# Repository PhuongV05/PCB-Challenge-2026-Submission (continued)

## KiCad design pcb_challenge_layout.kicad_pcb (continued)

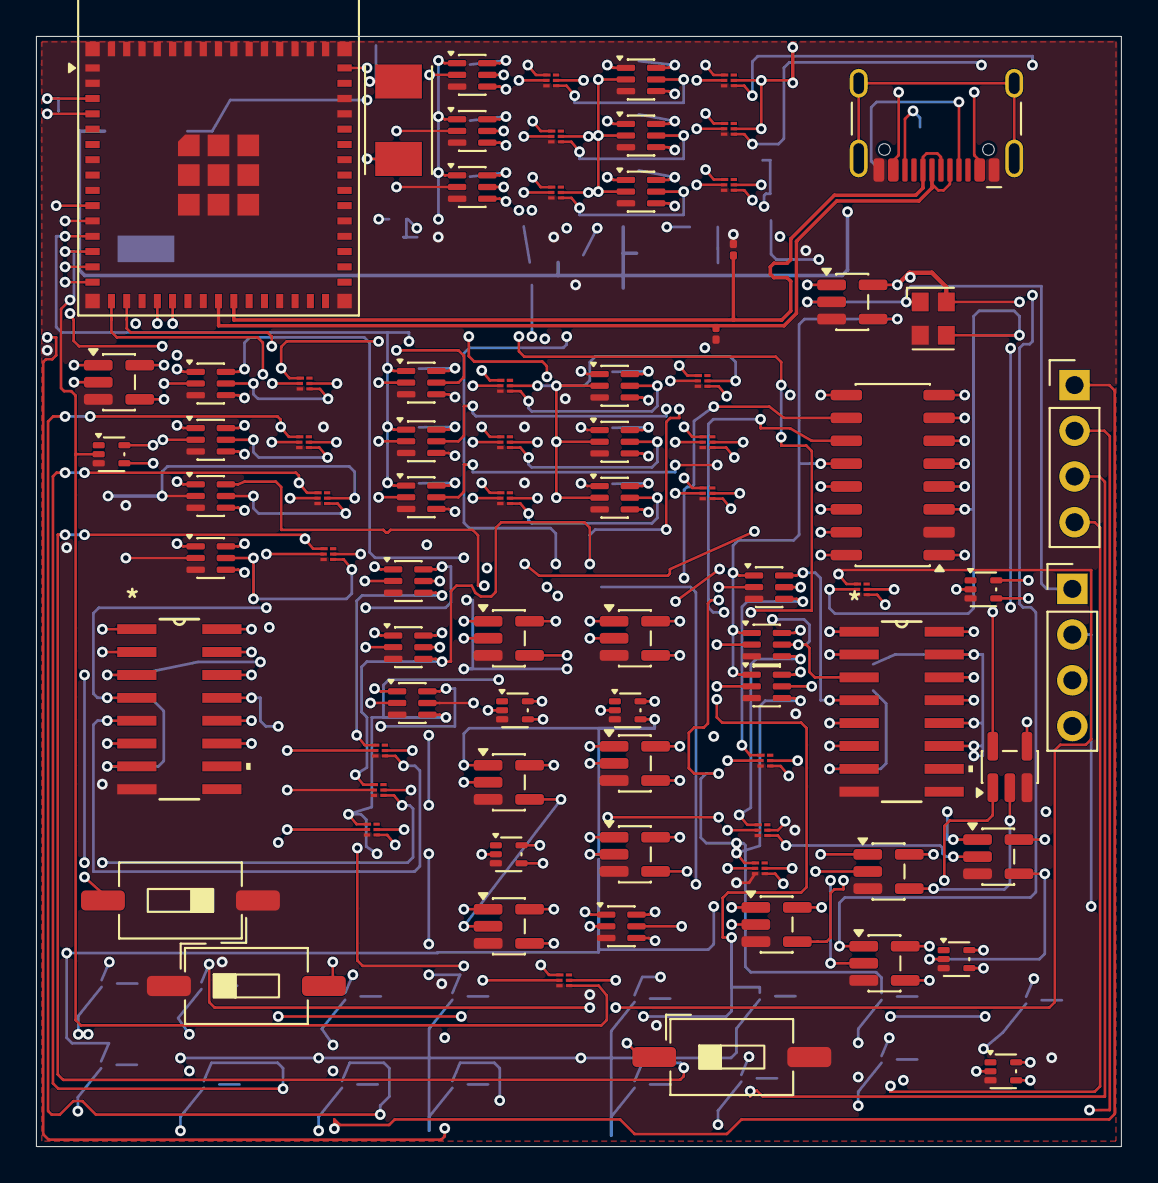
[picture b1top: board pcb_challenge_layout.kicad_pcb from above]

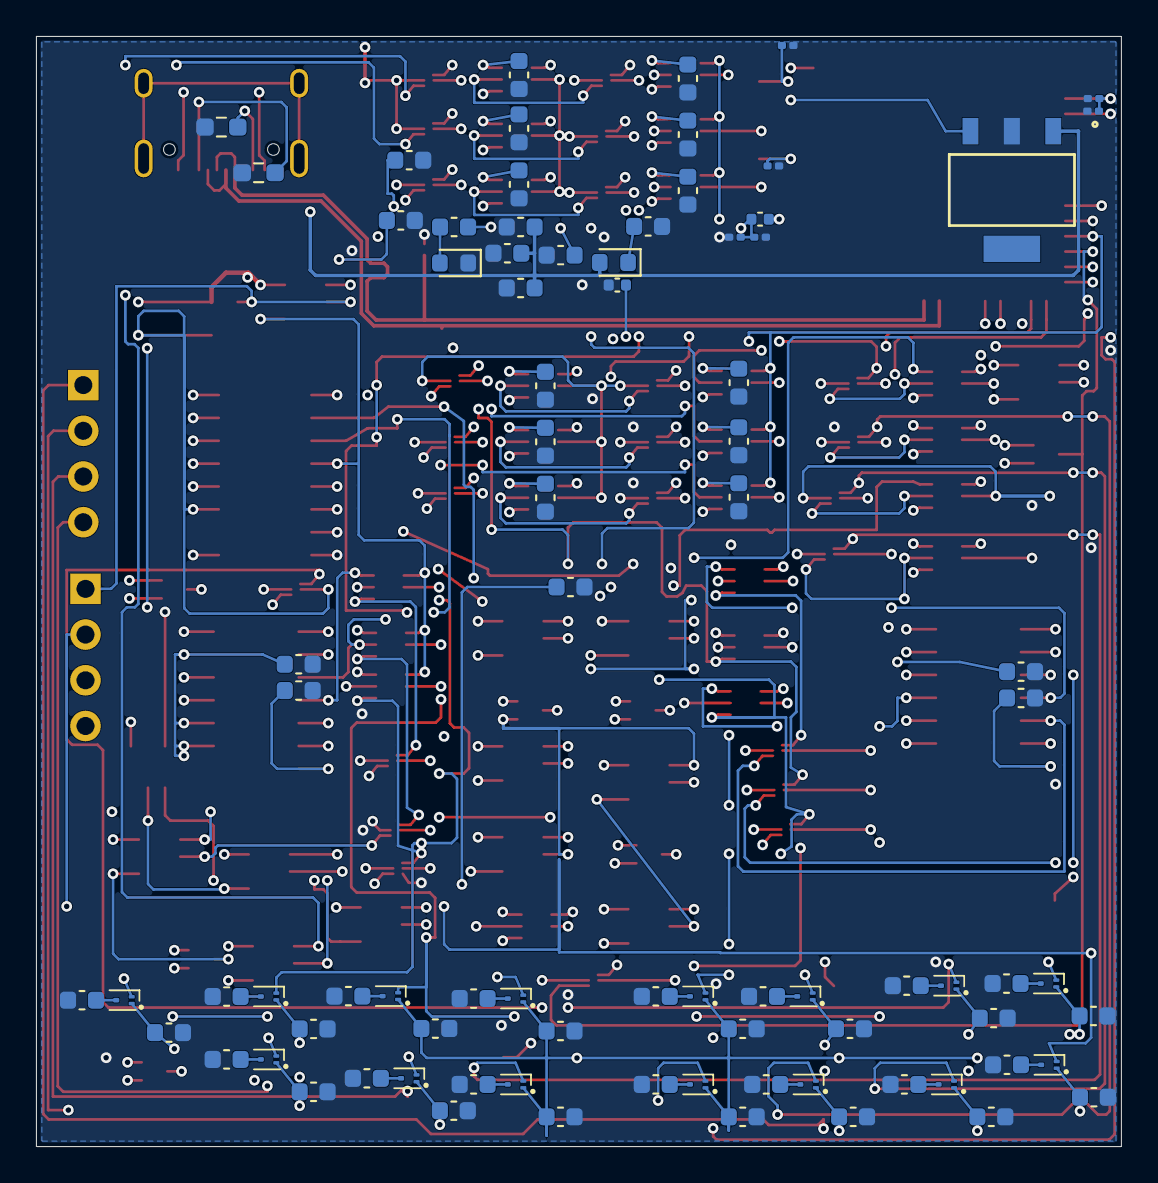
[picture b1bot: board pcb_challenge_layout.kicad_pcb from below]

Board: 4 copper layers, 60.3 x 61.7 mm, 164 parts (83 on the bottom side), 132 nets.
